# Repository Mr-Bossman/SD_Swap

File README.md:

# SD_Swap

## A development tool which swaps an SD card between a USB3 card reader and a SBC.

### About

SD_Swap allows reflashing of an SD card connected to the DUT (Device Under Test), without physical contact with the device. The board is designed in such way that it fits into micro SD card slots. Thanks to this, there is no need for special cables with a micro SD adapter, though it may be beneficial to add an extention to avoid accidentally breaking your boards SD connector if someone yanks the cable.

This project was inspired by the [SDWire](https://wiki.tizen.org/SDWire) project.
The major improvements are:
- USB-C
- USB3.0 read/write speeds
- Simplified design/control
- Solder jumpers to disconnect LEDs
- Dim LEDs so you wont get blinded

I have got SD write speeds up to 65MiB/s so 520Mbit/s

**IMPORTANT**

Faster SD cards may not work on some single board computers as the
timing and capacitance on the SBC side is not right.

### Rational

After seeing the [SDWire](https://wiki.tizen.org/SDWire) project I was disappointed by the complexity as well as the lack of USB3. So this project is uses the REALTEK RTS5306E controller which many USB3 to SD adapters use. The chip has power suspend functionality which we can use as a GPIO for switching hosts. The suspend option will shut off the SD cards power but not the controllers; it also has build-in RW protection as to finish writes before switching to the SBC

The SDWire project uses a USB to GPIO chip for this, but they have two power controlled USB ports on the board as well as the above mentioned method.

### Software
To swap the SD card between the host PC and the SBC you run
`sdswap -t` or `sdswap -c`.

 `-c` is the host PC while `-t` is the SBC. You can also chose which device to use if you have multiple attached. To do this run `lsusb` to show available the devices and type `sdswap -a 1-4 -c` in the format of `busNumber-deviceNumber`. I have future plans to write this script for Windows.

```
$ sdswap -h
Usage: sdswap [-h] [-p] [-c | -t] [-l location] [-a address] [-s serial] [-i VID:PID]
  -h, --help          Show this help message.
  -p, --print         Prints the block device
  -c, --controller    Switches to PC.
  -t, --target        Switchest to target.
  -l, --location      Set location.
  -a, --address       Set address.
  -s, --serial        Serial number.
  -i, --id            Set the PID and VID.
  -e, --exact         Use exact location.
If no options are given, the script will print the current status of the SDswap device.
If --print and --controller are given at the same time, the script will wait for the
SDswap device to be attached to the PC and then print the block device path.

Examples:
# sdswap
SDswap is attached to PC.

# sdswap -p
/dev/sda

# sdswap 0
Multiple devices found.

# sdswap -l 3-1.1 -t

# sdswap -a 3-19 -pc
/dev/sda
```

To manually controll the port use:

```
export YOUR_USB_NUM="1-4" #hub1 port4
echo 0 | sudo tee /sys/bus/usb/devices/${YOUR_USB_NUM}/power/autosuspend_delay_ms
echo auto | sudo tee /sys/bus/usb/devices/${YOUR_USB_NUM}/power/control

echo SBC
echo ${YOUR_USB_NUM} | sudo tee /sys/bus/usb/drivers/usb/unbind

echo PC
echo ${YOUR_USB_NUM} | sudo tee /sys/bus/usb/drivers/usb/bind
```
### Hardware
#### LEDs
 - D2 is the **red/blue** status LED it will be **blue** when the in passthrough mode, and **red** when the USB3 controller is reading/writing to it.
 - D1 is the **yellow** activity LED and blinks when the USB3 controller is reading/writing.
 - D3 is the **red** power LED and is active when the USB3 controller has power.

 **NOTE**: The **red** power LED will not be on if the USB cable isn't 5V providing power.

<!--

-->

### TODO
 - Fix SBC side timeing
 - Write program for Windows.
 - Fix serial number not working
 - Edit pick n' place csv
 - Label stat leds
 - Add use switching regulator
 - Add E-Fuse
 - Update readme

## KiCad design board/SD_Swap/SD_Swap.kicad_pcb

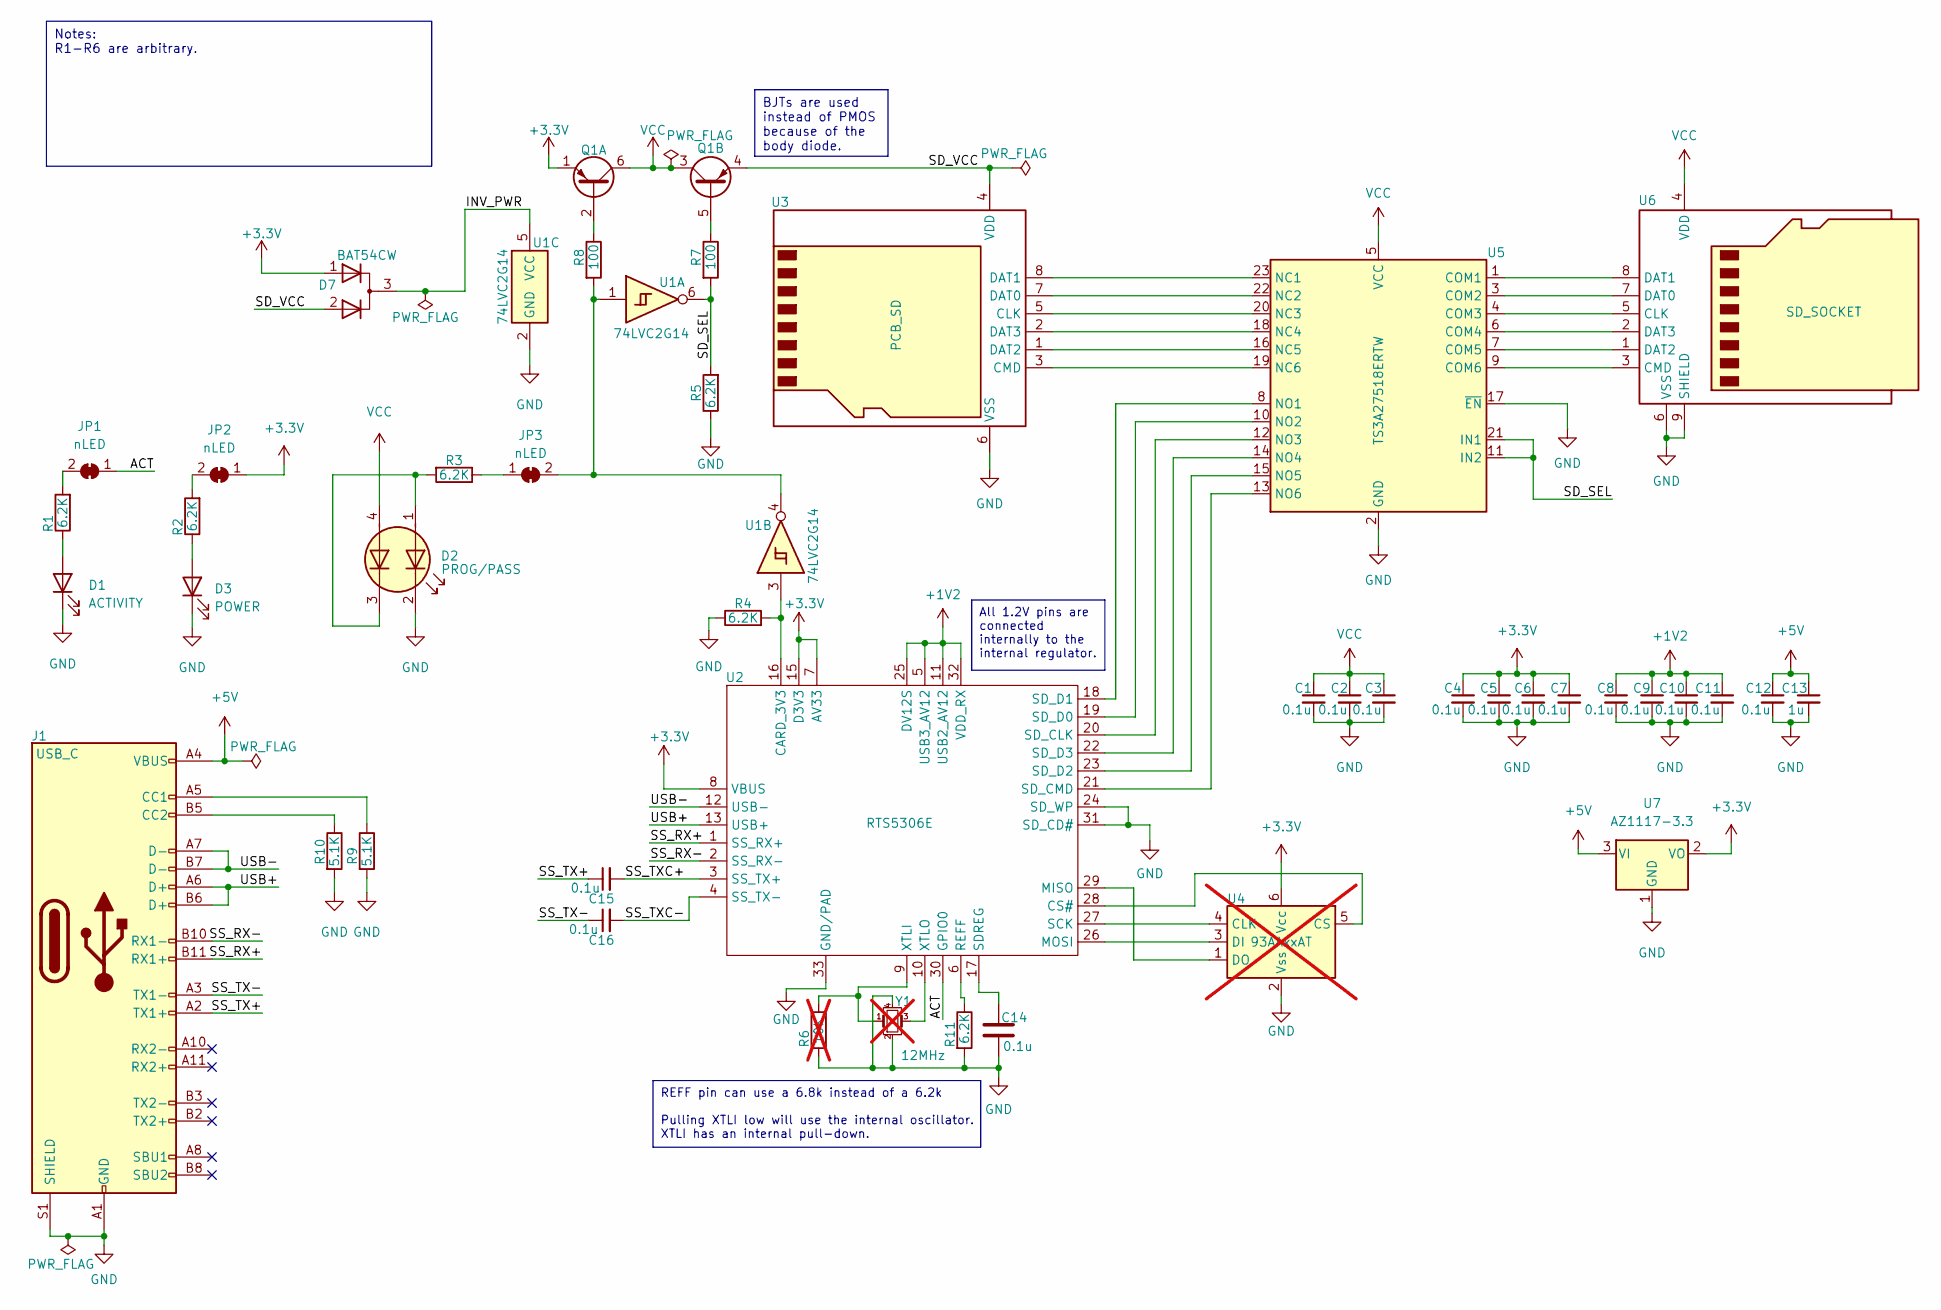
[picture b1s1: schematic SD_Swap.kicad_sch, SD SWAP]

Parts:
C1, C2, C3, C4, C5, C6, C7, C8, C9, C10, C11, C12, C14, C15, C16: 0.1u; C_0201_0603Metric; LCSC C66938
C13: 1u; C_0402_1005Metric; LCSC C107372
D1: ACTIVITY; LED_0603_1608Metric; LCSC C253534
D2: PROG/PASS; LED_RGB_1210; LCSC C264332
D3: POWER; LED_0603_1608Metric; LCSC C434419
D7: BAT54CW; SOT-323_SC-70; Part Number BAT54CW; LCSC C57891
J1: USB_C; USB_C_Receptacle_Amphenol_10137061-00021LF; Part Number 10137061-00021LF; LCSC C3197967
JP1, JP2, JP3: nLED; SolderJumper-2_P1.3mm_Bridged_RoundedPad1.0x1.5mm; Part Number NONE
Q1: Q_Dual_PNP_PNP_E1B1C2E2B2C1; SOT-23-6; Part Number QST8TR; LCSC C703623
R1, R2, R3: 6.2K; R_0603_1608Metric; LCSC C4260
R4, R5, R11: 6.2K; R_0201_0603Metric; LCSC C423334
R6: 10K; R_0603_1608Metric; not fitted
R7, R8: 100; R_0201_0603Metric; LCSC C2991668
R9, R10: 5.1K; R_0201_0603Metric; LCSC C100142
U1: 74LVC2G14; SOT-363_SC-70-6; Part Number 74LVC2G14; LCSC C3294721
U2: RTS5306E; VQFN-32-1EP_5x5mm_P0.5mm_EP3.5x3.5mm; Part Number RTS5306E; LCSC C2848856
U3: PCB_SD; PCB-SD; Part Number NONE
U4: 93AAxxAT; SOT-23-6; Part Number 93AA86AT; not fitted
U5: TS3A27518ERTW; WQFN-24-1EP_4x4mm_P0.5mm_EP2.6x2.6mm; Part Number TS3A27518ERTW; LCSC C2651937
U6: SD_SOCKET; 105162-0001; Part Number 105162-0001
U7: AZ1117-3.3; SOT-223-3_TabPin2; Part Number AZ1117CH-3.3TRG1; LCSC C92102
Y1: 12MHz; Resonator-3.2x1.3mm; Part Number CSTNE12M0G55A000R0; LCSC C907940; not fitted

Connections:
+1V2: C8.1, C9.1, C10.1, C11.1, U2.5 (USB3_AV12), U2.11 (USB2_AV12), U2.25 (DV12S), U2.32 (VDD_RX)
+3.3V: C4.1, C5.1, C6.1, C7.1, D7.1 (K), JP2.1 (A), Q1.1 (E1), U2.7 (AV33), U2.8 (VBUS), U2.14 (VBUS), U2.15 (D3V3), U4.6 (Vcc), U7.2 (VO)
+5V: C12.1, C13.1, J1.A4 (VBUS), J1.A9 (VBUS), J1.B4 (VBUS), J1.B9 (VBUS), U7.3 (VI)
/ACT: JP1.1 (A), U2.30 (GPIO0)
/INV_PWR: D7.3 (A), U1.5 (VCC)
/SD_SEL: R5.2, R7.2, U1.6, U5.11 (IN2), U5.21 (IN1)
/SD_VCC: D7.2 (K), Q1.4 (E2), U3.4 (VDD)
/SS_RX+: J1.B11 (RX1+), U2.1 (SS_RX+)
/SS_RX-: J1.B10 (RX1-), U2.2 (SS_RX-)
/SS_TX+: C15.1, J1.A2 (TX1+)
/SS_TX-: C16.1, J1.A3 (TX1-)
/SS_TXC+: C15.2, U2.3 (SS_TX+)
/SS_TXC-: C16.2, U2.4 (SS_TX-)
/USB+: J1.A6 (D+), J1.B6 (D+), U2.13 (USB+)
/USB-: J1.A7 (D-), J1.B7 (D-), U2.12 (USB-)
GND: C1.2, C2.2, C3.2, C4.2, C5.2, C6.2, C7.2, C8.2, C9.2, C10.2, C11.2, C12.2, C13.2, C14.2, D1.1 (K), D2.2 (K1), D3.1 (K), J1.A1 (GND), J1.A12 (GND), J1.B1 (GND), J1.B12 (GND), J1.S1 (SHIELD), R4.1, R5.1, R6.2, R9.2, R10.2, R11.2, U1.2 (GND), U2.24 (SD_WP), U2.31 (SD_CD#), U2.33 (GND/PAD), U3.6 (VSS), U4.2 (Vss), U5.2 (GND), U5.17 (~EN), U5.25 (GND), U6.6 (VSS), U6.9 (SHIELD), U6.10 (SHIELD), U6.11 (SHIELD), U6.12 (SHIELD), U6.13 (SHIELD), U6.14 (SHIELD), U6.15 (SHIELD), U7.1 (GND), Y1.2, Y1.4
unnamed: D1.2 (A), R1.1
unnamed: D2.1 (A1), D2.3 (K2), R3.2
unnamed: D3.2 (A), R2.1
unnamed: J1.A5 (CC1), R9.1
unnamed: J1.B5 (CC2), R10.1
unnamed: JP1.2 (B), R1.2
unnamed: JP2.2 (B), R2.2
unnamed: JP3.1 (A), R3.1
unnamed: JP3.2 (B), R8.2, U1.1, U1.4
unnamed: Q1.2 (B1), R8.1
unnamed: Q1.5 (B2), R7.1
unnamed: R4.2, U1.3, U2.16 (CARD_3V3)
unnamed: U2.28 (CS#), U4.5 (CS)
unnamed: U2.29 (MISO), U4.1 (DO)
unnamed: U2.26 (MOSI), U4.3 (DI)
unnamed: R11.1, U2.6 (REFF)
unnamed: U2.27 (SCK), U4.4 (CLK)
unnamed: C14.1, U2.17 (SDREG)
unnamed: U2.20 (SD_CLK), U5.12 (NO3)
unnamed: U2.21 (SD_CMD), U5.13 (NO6)
unnamed: U2.19 (SD_D0), U5.10 (NO2)
unnamed: U2.18 (SD_D1), U5.8 (NO1)
unnamed: U2.23 (SD_D2), U5.15 (NO5)
unnamed: U2.22 (SD_D3), U5.14 (NO4)
unnamed: R6.1, U2.9 (XTLI), Y1.1
unnamed: U2.10 (XTLO), Y1.3
unnamed: U3.5 (CLK), U5.20 (NC3)
unnamed: U3.3 (CMD), U5.19 (NC6)
unnamed: U3.7 (DAT0), U5.22 (NC2)
unnamed: U3.8 (DAT1), U5.23 (NC1)
unnamed: U3.1 (DAT2), U5.16 (NC5)
unnamed: U3.2 (DAT3), U5.18 (NC4)
unnamed: U5.1 (COM1), U6.8 (DAT1)
unnamed: U5.3 (COM2), U6.7 (DAT0)
unnamed: U5.4 (COM3), U6.5 (CLK)
unnamed: U5.6 (COM4), U6.2 (DAT3)
unnamed: U5.7 (COM5), U6.1 (DAT2)
unnamed: U5.9 (COM6), U6.3 (CMD)
VCC: C1.1, C2.1, C3.1, D2.4 (A2), Q1.3 (C2), Q1.6 (C1), U5.5 (VCC), U6.4 (VDD)

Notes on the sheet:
Notes: R1-R6 are arbitrary.
BJTs are used instead of PMOS because of the body diode.
All 1.2V pins are connected internally to the internal regulator.
REFF pin can use a 6.8k instead of a 6.2k Pulling XTLI low will use the internal oscillator. XTLI has an internal pull-down.

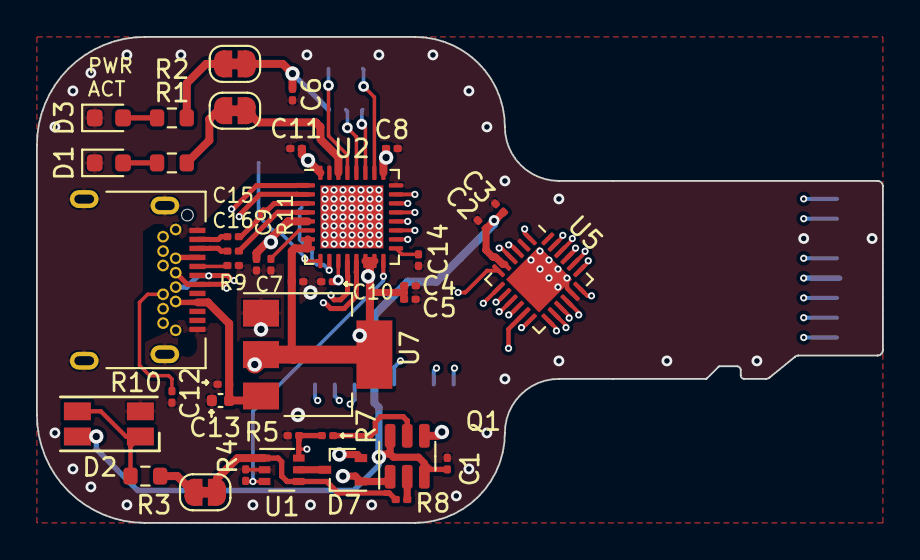
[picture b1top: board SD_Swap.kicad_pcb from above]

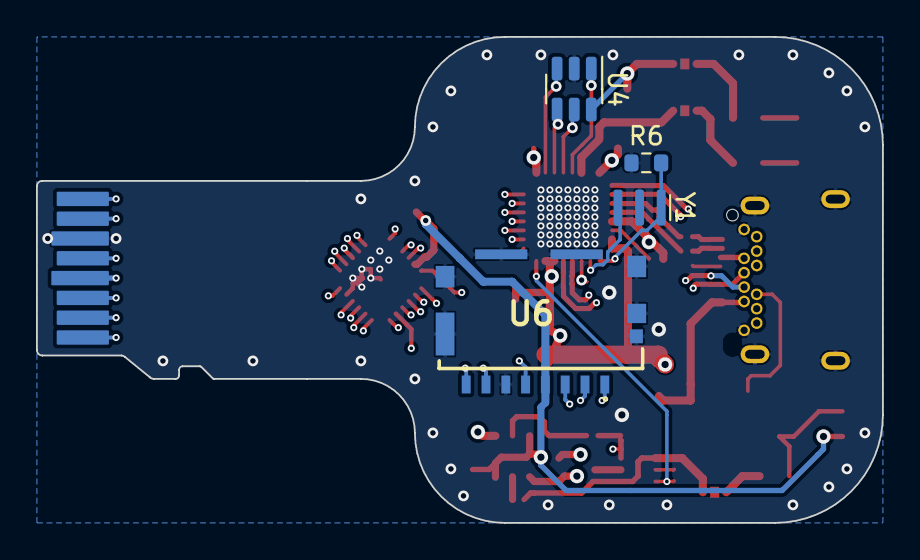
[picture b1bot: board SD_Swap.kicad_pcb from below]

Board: 4 copper layers, 47.0 x 27.0 mm, 44 parts (4 on the bottom side), 55 nets.

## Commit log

2022-12-16 Golden release candidate
2022-12-16 half way done with sch
2022-12-16 done with sch
2022-12-16 working on pcb add some caps to sch
2022-12-17 mostly done with the usb side of the brd
2022-12-17 doing more brd
2022-12-18 more sch and swap component sizes
2022-12-18 fix gerber folder
2022-12-18 add pcb-sd footprint add some notes in the sch
2022-12-19 add board mostly done
2022-12-19 add sdcard holder
2022-12-19 more routing
2022-12-20 more routing change osc and remove extra cap
2022-12-20 done with routing
2022-12-20 update BOM
2022-12-31 update fix led
2023-02-24 fixed clearance issue pnp base resistor is now 100R
2023-02-26 update SW and readme
2023-02-26 add TODO
2023-02-26 Update Readme and add images
2023-02-26 add help to swap.sh and add no dev found
2023-02-26 update sch
2023-03-26 add bigger reg to sch, update BOM,update todo
2023-09-01 update sch to use diodes to power the inverter
2023-09-01 update PCB to fix USB3 issues
2023-09-01 add images and pdfs
2023-09-01 export gerber
2023-12-09 I did USB-C wrong in the stupidest way
2023-12-12 tmp fix for my mistake
2024-01-13 final?
2024-01-13 add SD docs
2024-01-15 fix usbc
2024-01-24 remove pos files
2024-06-06 update gitignore
2024-06-06 update transistor
2024-06-06 update to kicad 8
2024-06-20 update TODO and images
2024-06-22 update vector plots
2024-06-29 update script
2024-06-29 update readme and todo. remove TODO file
2024-06-30 update docs
2024-06-30 add example
2024-10-17 update program add bisect example
2024-10-24 fix print
2025-06-09 sdswap: Update examples and sdswap script
    Script now uses getopt and has improved help message.
2025-06-09 sdswap: Add C version of sdswap program
    The C version allows for the control of the SDswap device
    on macOS and Linux systems.
2025-06-09 readme: Update to latest version of sdswap
    Update sdswap program example and explanation in README.md
    Update TODO
